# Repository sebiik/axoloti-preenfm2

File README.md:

# axoloti-preenfm2

Nothing to see here, carry on.

Edit: Well actually I got Axoloti to work well on the PreenFM2 but it included some nasty hardware hacking and a new, proper DAC chip plugged onto the P405 board, all of which is why I won't release any further info on this project.

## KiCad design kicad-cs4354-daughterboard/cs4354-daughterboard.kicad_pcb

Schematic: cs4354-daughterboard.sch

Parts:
3V3: 3V3; PinHeader_1x01_P2.54mm_Vertical
B_GND_A1: L GND R; PinHeader_1x04_P2.54mm_Vertical
C1, C4: 100nF; C_0805_2012Metric_Pad1.15x1.40mm_HandSolder
C2, C3, C5, C6: 2.2uF; C_0805_2012Metric_Pad1.15x1.40mm_HandSolder
C7, C8: 2.2nF; C_0805_2012Metric_Pad1.15x1.40mm_HandSolder
GND1: GND; PinHeader_1x01_P2.54mm_Vertical
H1, H2: MountingHole; MountingHole_2.5mm
J8: 5VA; PinHeader_1x01_P2.54mm_Vertical
LRCK1: LRCK; PinHeader_1x01_P2.54mm_Vertical
MCK1: MCK; PinHeader_1x01_P2.54mm_Vertical
R1, R2: 470R; R_0805_2012Metric_Pad1.15x1.40mm_HandSolder
R3, R4, R5, R6: DNP; R_0805_2012Metric_Pad1.15x1.40mm_HandSolder
SCK1: SCK; PinHeader_1x01_P2.54mm_Vertical
SDI1: SDI; PinHeader_1x01_P2.54mm_Vertical
U1: CS4354; SOIC-14_3.9x8.7mm_P1.27mm

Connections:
+3V3: 3V3.1, C1.1, R3.2, R4.2, R5.2, R6.2, U1.1 (VL)
+5VA: C4.1, C6.1, J8.1, U1.11 (VA)
/1_VOUT_A(to1.8K): B_GND_A1.4, C8.1, R2.1
/2_VOUT_A(to1.8K): B_GND_A1.1, C7.1, R1.1
GND: B_GND_A1.2, B_GND_A1.3, C1.2, C2.2, C3.1, C4.2, C6.2, C7.2, C8.2, GND1.1, U1.6 (GND), U1.10 (GND)
unnamed: C2.1, U1.7 (FILT+)
unnamed: C3.2, U1.14 (-VFILT)
unnamed: C5.1, U1.12 (FLYP)
unnamed: C5.2, U1.13 (FLYN)
unnamed: LRCK1.1, R5.1, U1.4 (LRCLK)
unnamed: MCK1.1, R4.1, U1.3 (MCLK)
unnamed: R1.2, U1.9 (AOUTB)
unnamed: R2.2, U1.8 (AOUTA)
unnamed: R3.1, SDI1.1, U1.2 (SDIN)
unnamed: R6.1, SCK1.1, U1.5 (SCLK/DEM)

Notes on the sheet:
pullups (do not place unless something isn't working)

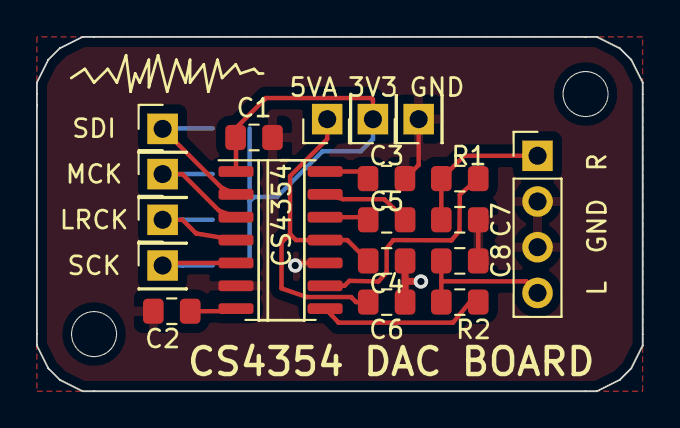
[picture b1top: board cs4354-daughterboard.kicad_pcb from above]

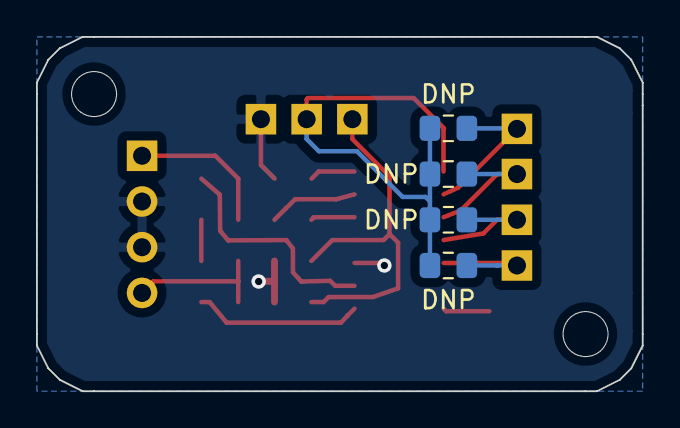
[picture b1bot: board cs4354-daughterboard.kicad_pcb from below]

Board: 2 copper layers, 33.7 x 19.7 mm, 25 parts (4 on the bottom side), 15 nets.

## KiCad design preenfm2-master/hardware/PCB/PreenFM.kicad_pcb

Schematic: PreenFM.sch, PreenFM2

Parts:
3V1: LD1117
5V1: 7805
AJ1, AJ2: AUDIO_JACK
C1, C2, C3, C5, C7, C8, C10, C14, C19, C23: 100nF
C4: PreenF405/CERB40
C6, C9, C11, C13, C22: 220uF
C12: 330nF
C15, C16: 1nF
C17, C18: 3.3nF
C20, C21: 22uF
D1: 1N4148
D2, D3: 1N4001
DAC1, DAC2: MCP4922
DC1: DC
Enc1, Enc2, Enc3, Enc4: ENCODER_SW
IC1, IC2: 74HC165N; 74xx-eu-DIL16
J1: USB_1
Jmp1, Jmp2, Jmp3: Jmp
K2: USB
L1: 10uH
L2, L3, L4, L5: LED
LCD1: Disp 20x4
M1: In
M2: Out
OC1: 6N137; optocoupler-DIL08
P1, P3: CONN_5
P4, P5, P6, P7: CONN_1
POW1: 5V
R1, R2, R3, R6: 220
R4, R5: 10k
R7, R9: 1.8k
R8, R10: 115k
R11, R14, R15: 68
R12, R13: 8.2k
R16, R17: 1M
R18: 22
R19: Oled
RR1, RR2: RR10k
RV1: 10k
S1, S2, S3, S4, S5, S6, S7: SWITCH
U1: USBKey
V1: VOLUME
op1: OpAmp

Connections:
+3.3V: 3V1.2 (Vout), C1.1, C2.1, C4.1 (3.3V), C4.16 (PB8), C9.1, C23.1, IC1.16 (VCC), IC2.16 (VCC), Jmp3.2, P1.1, P3.1, R1.2, R4.1, RR1.1, RR2.1
+5V: C6.1, C7.1, C8.1, C19.1, DAC1.1 (Vdd), DAC2.1 (Vdd), L1.2, R6.1, op1.8 (VCC)
+5VA: 3V1.3 (Vin), 5V1.2 (Vout), C3.1, C5.1, C10.1, C22.1, D3.1 (K), Jmp2.1, L1.1, OC1.8 (VCC), POW1.1, R5.2, R11.2, R19.2, RV1.3, U1.1
/AIN1: C4.22 (PC0), P3.2
/AIN2: C4.23 (PC1), P3.3
/AIN3: C4.24 (PC2), P3.4
/AIN4: C4.25 (PC3), P3.5
/DB4: C4.28 (PA2), LCD1.11 (DB4)
/DB5: C4.29 (PA3), LCD1.12 (DB5)
/DB6: C4.30 (PA4), LCD1.13 (DB6)
/DB7: C4.31 (PA5), LCD1.14 (DB7)
/E: C4.27 (PA1), LCD1.6 (E)
/LED: C4.19 (PB6), R18.1
/LODR: C4.17 (LODR), Jmp3.1
/MCLK: C4.3 (PA8), IC1.2 (CLK), IC2.2 (CLK)
/MLD: C4.6 (PA6), IC1.1 (SH/LD\), IC2.1 (SH/LD\)
/MQH: C4.5 (PA7), IC1.9 (QH)
/RESET: C4.21 (REST), P1.5
/RR1_1: IC1.14 (D), RR1.2, S2.2
/RR1_2: IC1.3 (E), RR1.3, S1.2
/RR1_3: Enc1.3, Enc2.3, Enc3.3, Enc4.3, IC1.13 (C), RR1.4
/RR1_4: Enc4.2 (Pin2), IC1.4 (F), RR1.5
/RR1_5: Enc4.0 (Pin1), IC1.12 (B), RR1.6
/RR1_6: Enc3.2 (Pin2), IC1.5 (G), RR1.7
/RR1_7: Enc3.0 (Pin1), IC1.11 (A), RR1.8
/RR1_8: Enc2.2 (Pin2), IC1.6 (H), RR1.9
/RR2_1: Enc2.0 (Pin1), IC2.14 (D), RR2.2
/RR2_2: Enc1.2 (Pin2), IC2.3 (E), RR2.3
/RR2_3: Enc1.0 (Pin1), IC2.13 (C), RR2.4
/RR2_4: IC2.4 (F), RR2.5, S3.2
/RR2_5: IC2.12 (B), RR2.6, S4.2
/RR2_6: IC2.5 (G), RR2.7, S5.2
/RR2_7: IC2.11 (A), RR2.8, S6.2
/RR2_8: IC2.6 (H), RR2.9, S7.2
/RS: C4.26 (PA0), LCD1.4 (RS)
/RX: C4.33 (PB11), OC1.6 (VO), R5.1
/SPI_CK: C4.12 (PB3), DAC1.4 (SCK), DAC2.4 (SCK)
/SPI_DAC1: C4.10 (PB4), DAC1.3 (CS)
/SPI_DAC2: C4.11 (PB9), DAC2.3 (CS)
/SPI_LDAC: C4.14 (PC12), DAC1.8 (LDAC), DAC2.8 (LDAC)
/SPI_MO: C4.20 (PB5), DAC1.5 (SDI), DAC2.5 (SDI)
/SWD_CLK: C4.8 (PA14), P1.2
/SWD_IO: C4.4 (PA13), P1.4
/TX: C4.32 (PB10), R3.2
/USB_D+: C4.39 (PC9), J1.3, K2.1
/USB_D-: C4.38 (PC8), J1.2, K2.2
/USB_DN: C4.34 (PB14), U1.2
/USB_DP: C4.35 (PB15), U1.3
GND: 3V1.1 (GND), 5V1.1 (GND), AJ1.0 (Gnd), AJ2.0 (Gnd), C1.2, C2.2, C3.2, C4.2 (GND), C5.2, C6.2, C7.2, C8.2, C9.2, C10.2, C11.2, C12.2, C13.2, C14.2, C15.2, C16.2, C19.2, C22.2, C23.2, DAC1.12 (AVss), DAC2.12 (AVss), DC1.1, Enc1.1 (GND), Enc1.4, Enc2.1 (GND), Enc2.4, Enc3.1 (GND), Enc3.4, Enc4.1 (GND), Enc4.4, IC1.8 (GND), IC1.15 (INH), IC2.8 (GND), IC2.15 (INH), J1.4, L2.2 (A), L3.2 (A), L4.2 (A), L5.2 (A), LCD1.1 (VSS), LCD1.5 (R/W), LCD1.7 (DB0), LCD1.8 (DB1), LCD1.9 (DB2), LCD1.10 (DB3), LCD1.16 (K), OC1.5 (GND), P1.3, POW1.2, R16.2, R17.2, RV1.1, S1.1, S2.1, S3.1, S4.1, S5.1, S6.1, S7.1, U1.4, V1.1, V1.4, op1.4 (GND)
unnamed: IC1.10 (SER), IC2.9 (QH), R4.2
unnamed: AJ1.1 (Audio1), V1.5
unnamed: M2.1, R1.1
unnamed: C17.1, R14.1, op1.1, op1.2 (-)
unnamed: C18.1, R15.1, op1.6 (-), op1.7
unnamed: C20.1, R14.2
unnamed: C21.1, R15.2
unnamed: DAC1.14 (VoutA), R7.1
unnamed: C15.1, R13.2, op1.5 (+)
unnamed: DAC2.14 (VoutA), R9.1
unnamed: DAC2.10 (voutB), R10.1
unnamed: DAC1.10 (voutB), R8.1
unnamed: C17.2, R7.2, R8.2, R12.1
unnamed: AJ2.1 (Audio1), V1.2
unnamed: C20.2, R16.1, V1.6
unnamed: D2.1 (K), Jmp1.2
unnamed: DC1.3, Jmp1.1
unnamed: LCD1.15 (A), R11.1
unnamed: C16.1, R12.2, op1.3 (+)
unnamed: J1.1, Jmp2.2
unnamed: LCD1.3 (VO), RV1.2
unnamed: M1.1, R2.1
unnamed: M2.2, R3.1
unnamed: D1.1 (K), M1.2, OC1.3 (C)
unnamed: C18.2, R9.2, R10.2, R13.1
unnamed: 5V1.3 (Vin), C12.1, D2.2 (A), D3.2 (A)
unnamed: C21.2, R17.1, V1.3
unnamed: C11.1, C13.1, DAC1.11 (VrefB), DAC1.13 (VrefA), DAC2.11 (VrefB), DAC2.13 (VrefA), R6.2
unnamed: L2.1 (K), L3.1 (K), L4.1 (K), L5.1 (K), R18.2

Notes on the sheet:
GND/5V
Analog input
Audio Path
LCD 4x20
PCB hole
USB Key plug
SWD Debug
MIDI
POWER
Surface control
FEZ Cerb40 / PreenF405
LED
Enter Bootloader

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
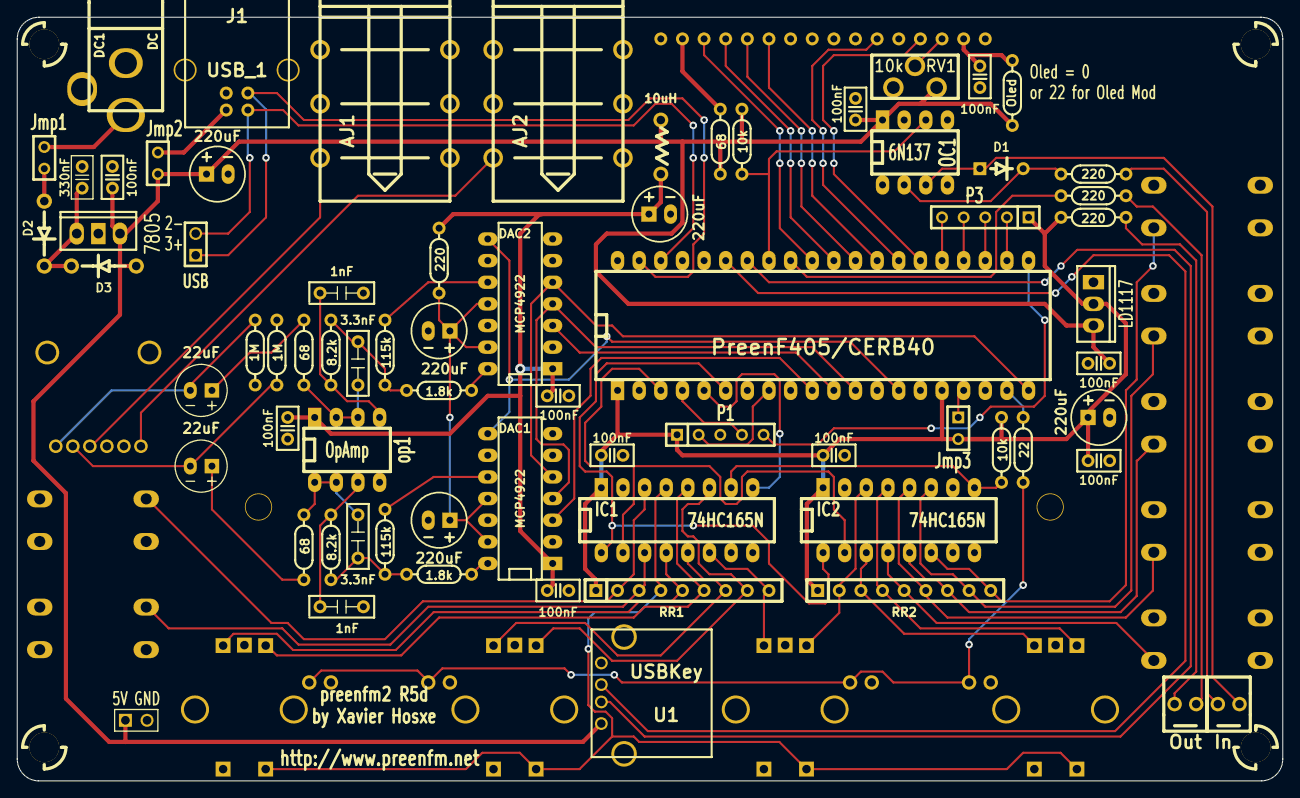
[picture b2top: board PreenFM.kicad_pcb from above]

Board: 2 copper layers, 148.6 x 89.7 mm, 92 parts (0 on the bottom side), 80 nets.

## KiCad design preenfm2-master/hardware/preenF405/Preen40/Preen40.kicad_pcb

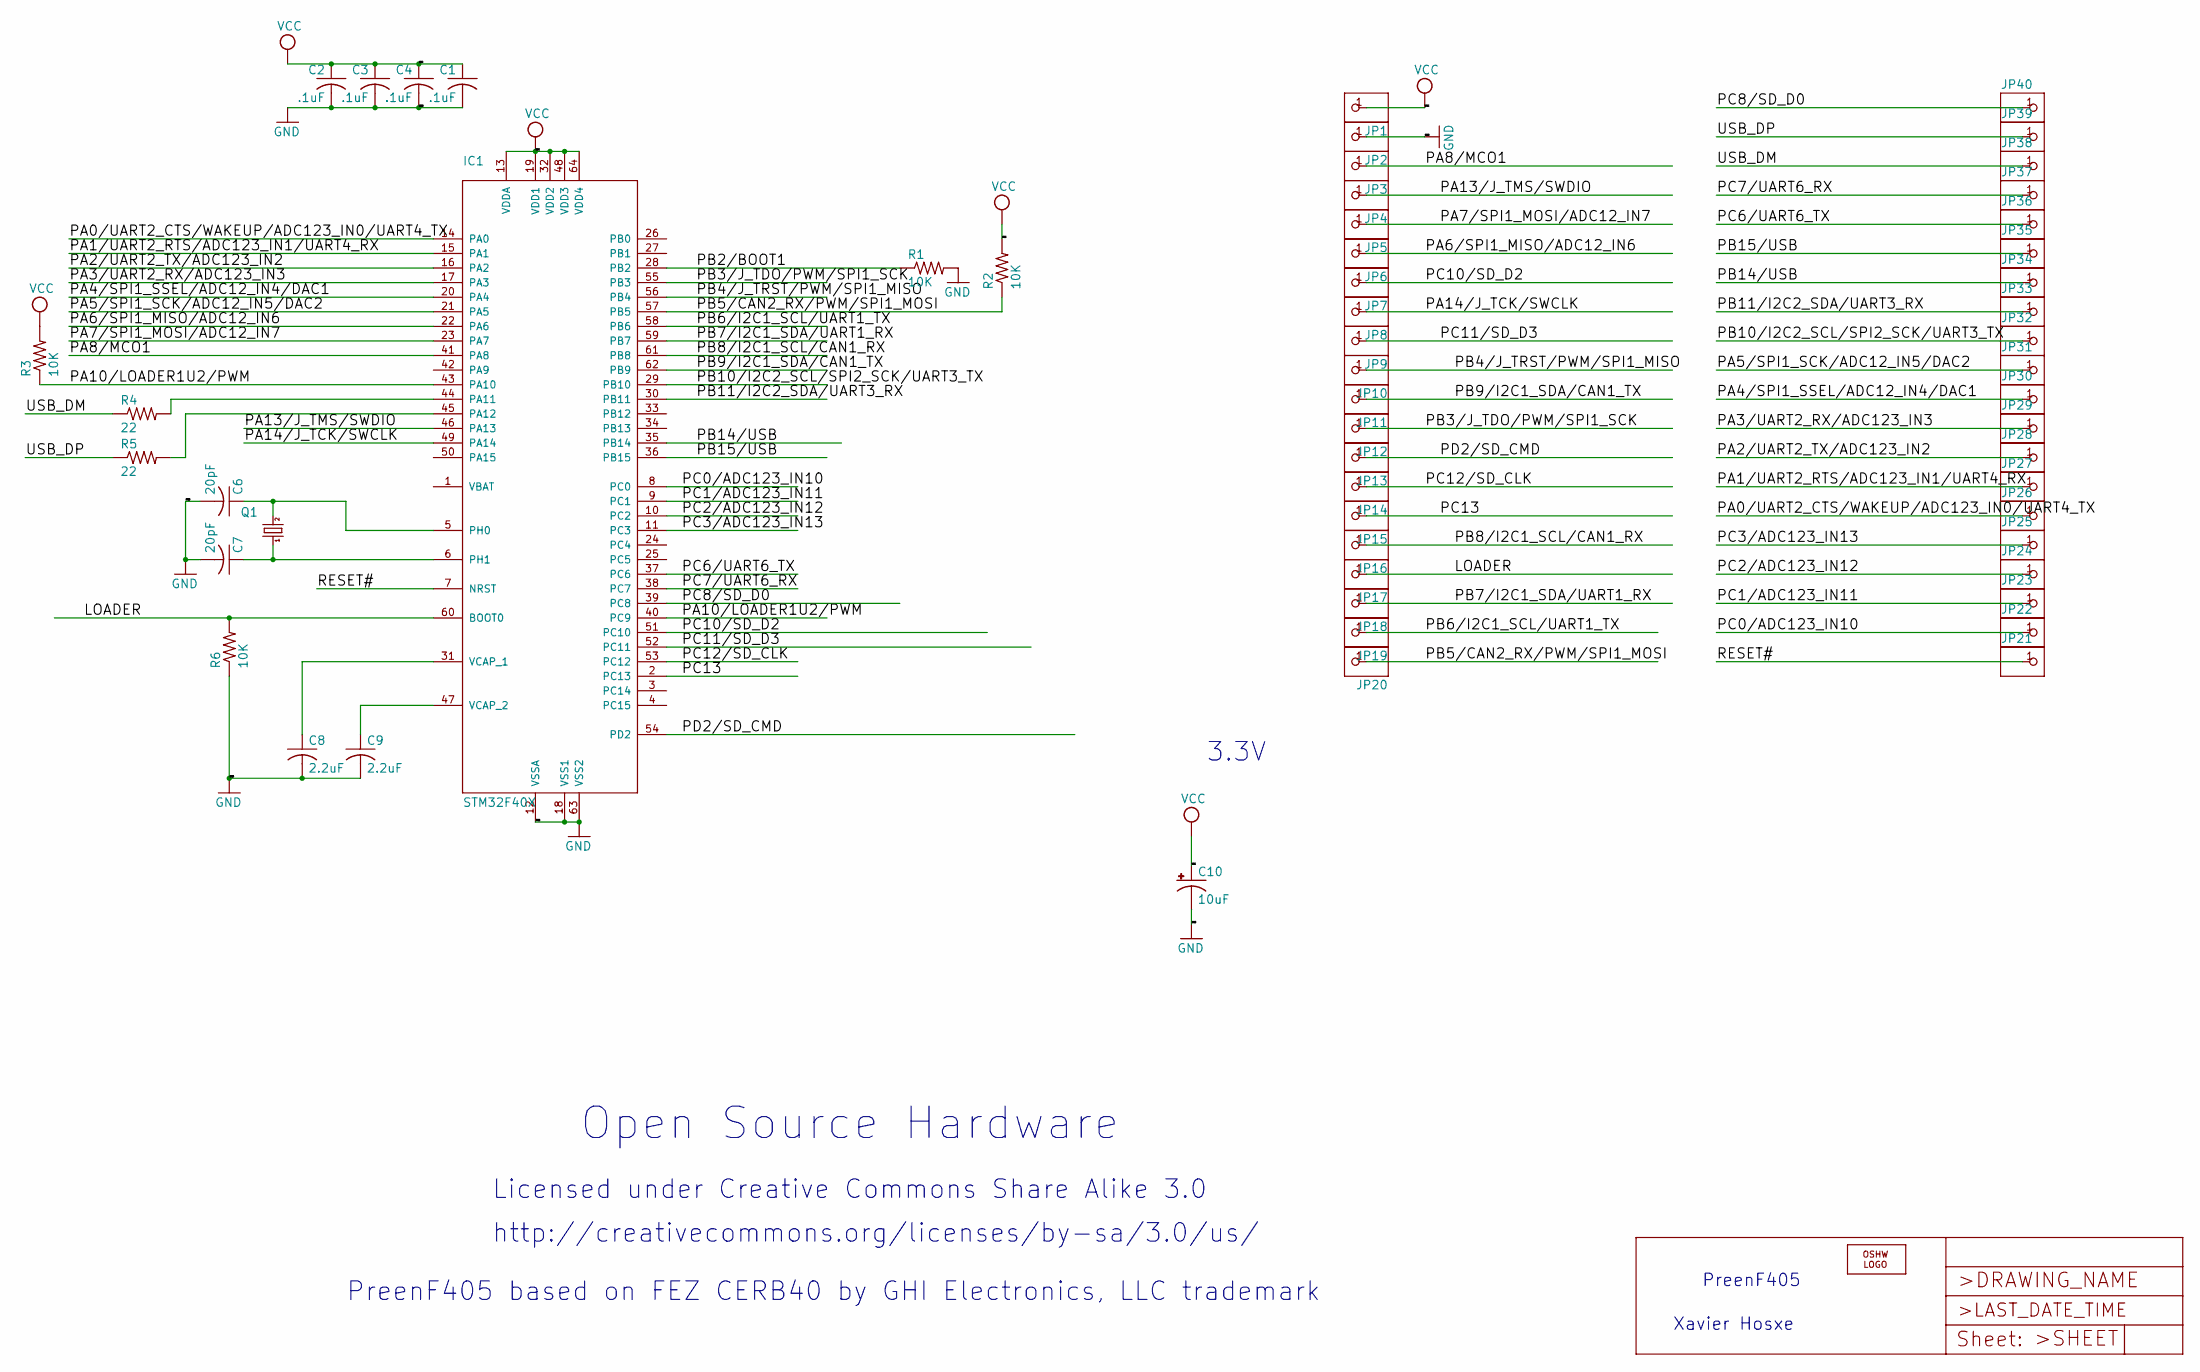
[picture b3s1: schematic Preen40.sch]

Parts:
C1, C2, C3, C4: .1uF; C0603K
C6, C7: 20pF; C0603K
C8, C9: 2.2uF; C0805K
C10: 10uF; CT3528
IC1: STM32F40X; LQFP64
JP1, JP2, JP3, JP4, JP5, JP6, JP7, JP8, JP9, JP10, JP11, JP12, JP13, JP14, JP15, JP16, JP17, JP18, JP19, JP20, JP21, JP22, JP23, JP24, JP25, JP26, JP27, JP28, JP29, JP30, JP31, JP32, JP33, JP34, JP35, JP36, JP37, JP38, JP39, JP40: PINHD-1X1; 1X01
LOGO1: LOGO-OSHW-FILLX0200-NT; OSHW_FILLX200_NOTEXT
Q1: 12Mhz; SM49@1
R1, R2, R3, R6: 10K; R0603
R4, R5: 22; R0603

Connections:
/LOADER: IC1.60 (BOOT0), JP17.1, R6.2
/PA0/UART2_CTS/WAKEUP/ADC123_IN0/UART4_TX: IC1.14 (PA0), JP26.1
/PA1/UART2_RTS/ADC123_IN1/UART4_RX: IC1.15 (PA1), JP27.1
/PA2/UART2_TX/ADC123_IN2: IC1.16 (PA2), JP28.1
/PA3/UART2_RX/ADC123_IN3: IC1.17 (PA3), JP29.1
/PA4/SPI1_SSEL/ADC12_IN4/DAC1: IC1.20 (PA4), JP30.1
/PA5/SPI1_SCK/ADC12_IN5/DAC2: IC1.21 (PA5), JP31.1
/PA6/SPI1_MISO/ADC12_IN6: IC1.22 (PA6), JP6.1
/PA7/SPI1_MOSI/ADC12_IN7: IC1.23 (PA7), JP5.1
/PA8/MCO1: IC1.41 (PA8), JP3.1
/PA10/LOADER1U2/PWM: IC1.40 (PC9), IC1.43 (PA10), R3.1
/PA13/J_TMS/SWDIO: IC1.46 (PA13), JP4.1
/PA14/J_TCK/SWCLK: IC1.49 (PA14), JP8.1
/PB2/BOOT1: IC1.28 (PB2), R1.1
/PB3/J_TDO/PWM/SPI1_SCK: IC1.55 (PB3), JP12.1
/PB4/J_TRST/PWM/SPI1_MISO: IC1.56 (PB4), JP10.1
/PB5/CAN2_RX/PWM/SPI1_MOSI: IC1.57 (PB5), JP20.1, R2.1
/PB6/I2C1_SCL/UART1_TX: IC1.58 (PB6), JP19.1
/PB7/I2C1_SDA/UART1_RX: IC1.59 (PB7), JP18.1
/PB8/I2C1_SCL/CAN1_RX: IC1.61 (PB8), JP16.1
/PB9/I2C1_SDA/CAN1_TX: IC1.62 (PB9), JP11.1
/PB10/I2C2_SCL/SPI2_SCK/UART3_TX: IC1.29 (PB10), JP32.1
/PB11/I2C2_SDA/UART3_RX: IC1.30 (PB11), JP33.1
/PB14/USB: IC1.35 (PB14), JP34.1
/PB15/USB: IC1.36 (PB15), JP35.1
/PC0/ADC123_IN10: IC1.8 (PC0), JP22.1
/PC1/ADC123_IN11: IC1.9 (PC1), JP23.1
/PC2/ADC123_IN12: IC1.10 (PC2), JP24.1
/PC3/ADC123_IN13: IC1.11 (PC3), JP25.1
/PC6/UART6_TX: IC1.37 (PC6), JP36.1
/PC7/UART6_RX: IC1.38 (PC7), JP37.1
/PC8/SD_D0: IC1.39 (PC8), JP40.1
/PC10/SD_D2: IC1.51 (PC10), JP7.1
/PC11/SD_D3: IC1.52 (PC11), JP9.1
/PC12/SD_CLK: IC1.53 (PC12), JP14.1
/PC13: IC1.2 (PC13), JP15.1
/PD2/SD_CMD: IC1.54 (PD2), JP13.1
/RESET#: IC1.7 (NRST), JP21.1
/USB_DM: JP38.1, R4.1
/USB_DP: JP39.1, R5.1
GND: C1.2, C2.2, C3.2, C4.2, C6.2, C7.2, C8.2, C9.2, C10.-, IC1.12 (VSSA), IC1.18 (VSS1), IC1.63 (VSS2), JP2.1, R1.2, R6.1
unnamed: C6.1, IC1.5 (PH0), Q1.2
unnamed: C7.1, IC1.6 (PH1), Q1.1
unnamed: C8.1, IC1.31 (VCAP_1)
unnamed: C9.1, IC1.47 (VCAP_2)
unnamed: IC1.44 (PA11), R4.2
unnamed: IC1.45 (PA12), R5.2
VCC: C1.1, C2.1, C3.1, C4.1, C10.+, IC1.13 (VDDA), IC1.19 (VDD1), IC1.32 (VDD2), IC1.48 (VDD3), IC1.64 (VDD4), JP1.1, R2.2, R3.2

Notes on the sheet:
PreenF405
Xavier Hosxe
Open Source Hardware
Licensed under Creative Commons Share Alike 3.0
PreenF405 based on FEZ CERB40 by GHI Electronics, LLC trademark
http://creativecommons.org/licenses/by-sa/3.0/us/
3.3V

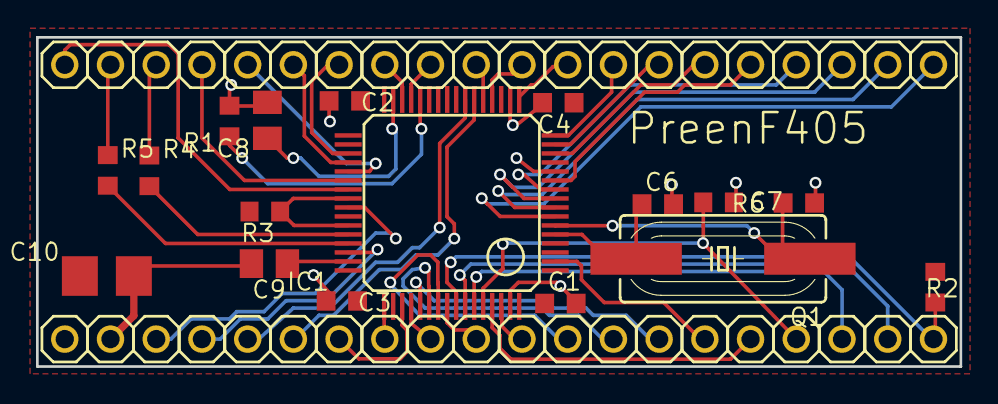
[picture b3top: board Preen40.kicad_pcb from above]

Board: 2 copper layers, 51.3 x 18.3 mm, 58 parts (0 on the bottom side), 48 nets.

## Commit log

2019-06-20 add BOARD_PREENFM2 option to defines
2019-06-21 commented out some pin assigments
2019-06-26 fork board_preenfm2.h file, include preenfm2 repository for reference
2019-07-02 design daughterboard for CS4354 DAC
2019-07-02 renamed kicad daughterboard 'noDIL'
2019-07-05 change I2S codec to CS4354 DAC
2019-10-04 cs4354 daughterboard fix, axo-preenfm2 analog input now working
